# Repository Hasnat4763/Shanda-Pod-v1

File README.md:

# Shanda Pod

It is an MP3 player which can also play audio via bluetooth A2DP source and a PCM5102A module

I made this project because I wanted to experiment with mp3 players and I need an mp3 player with bluetooth outputs

# PCB

This is the Schematic

This is the PCB

PCB 3D View

# CAD

I designed it in Fusion360 which was pretty hard as it crashed idk why
This is all the parts fitted together

This is a cover which will sit on top of the battery

# Schematic

I have some parts outside of my PCB

# BOM

| Name                                                                  | Qty | Final Price - USD(BDT) | Link                                                                                                                |
| --------------------------------------------------------------------- | --- | ----------------------- | ------------------------------------------------------------------------------------------------------------------- |
| ESP-32-WROVER-E                                                       | 1   | US $7.39                | [here](https://www.aliexpress.com/item/1005008347478258.html?spm=a2g0o.cart.0.0.35b638daQUHsS4&mp=1)                                                             |
| NASAYI 10pcs/lot DM3AT-SF-PEJM5                                       | 10  | US $8.63                | [here](https://www.aliexpress.com/item/1005009250329013.html?spm=a2g0o.cart.0.0.35b638daQUHsS4&mp=1&pdp_ext_f=%7B%22cart2PdpParams%22%3A%7B%22pdpBusinessMode%22%3A%22retail%22%7D%7D)                                  |
| CH340C sop-16 Chipset                                                 | 5   | US $1.44                | [here](https://www.aliexpress.com/item/1005004970840775.html?spm=a2g0o.cart.0.0.35b638daQUHsS4&mp=1)                                           |
| 6092 bq25185 USB / DC / Solar Charger with 3.3V Buck Board            | 1   | US $13.66               | [here](https://www.aliexpress.com/item/1005008651296534.html?spm=a2g0o.cart.0.0.35b638daQUHsS4&mp=1)                                                                |
| 100NF 0.1UF 50V C0805 Capacitor                                       | 100 | US $0.73                | [here](https://www.aliexpress.com/item/1115774532.html?spm=a2g0o.cart.0.0.35b638daQUHsS4&mp=1)                                                                                   |
|  SSD1306                                                              | 1   | US $1.42                | [here](https://www.aliexpress.com/item/1005003780343300.html?spm=a2g0o.cart.0.0.35b638daQUHsS4&mp=1)                                                                                   |
| PCM5102A DAC                                                          | 1   | US $4.05                | [here](https://www.aliexpress.com/item/1005006104368969.html?spm=a2g0o.cart.0.0.35b638daQUHsS4&mp=1)                                                                                   |
| Insert M1.6 Brass Heat Threaded Insert Nut and Stainless Steel Screw  |set  | US $15.02               | [here](https://www.aliexpress.com/item/1005004837433548.html?spm=a2g0o.cart.0.0.35b638daQUHsS4&mp=1)                                                                                   |
| MHP30 Mini Hot Plate                                                  | 1   | US $13.52               | [here](https://www.aliexpress.com/item/1005005887052045.html?spm=a2g0o.cart.0.0.72f938daHYVVmK&mp=1)          |
| 18650 Lithium-ion                                                     | 2   | 348 BDT                 | [here](https://www.daraz.com.bd//products/i337388376-s1645620986.html?spm=a2o42.cart.0.0.5b8f282903B5mN&urlFlag=true&tradePath=%2CcartPriceDrop%2Ccart)                                           |
| PCB                                                                   | 5   | US $26.68               | [here](https://hc-cdn.hel1.your-objectstorage.com/s/v3/ba1be02d5d65575ba7409b266db8009ed1d59e8f_image.png)                                          |
| Stencil                                                               | 1   | US $$8.90               | [here](https://hc-cdn.hel1.your-objectstorage.com/s/v3/ba1be02d5d65575ba7409b266db8009ed1d59e8f_image.png)                                         |                                                                                 |
| Soldering Paste                                                       | 1   | US $3.81                | [here](https://www.aliexpress.com/item/1005009298760047.html?spm=a2g0o.productlist.main.11.11a96444UURzz6&algo_pvid=175fc725-feab-48a3-bc75-27a2c631128b&pdp_ext_f=%7B%22order%22%3A%22880%22%2C%22eval%22%3A%221%22%7D&utparam-url=scene%3Asearch%7Cquery_from%3A)                                         |        
| Top Case                                                              | 1   | Printing Legion         | 
| Bottom Case                                                           | 1   | Printing Legion         |
| Battery Cover                                                         | 1   | Printing Legion         |

# Total Cost: ~ 115$ USD

# Why is this too exbensive?

Check this out

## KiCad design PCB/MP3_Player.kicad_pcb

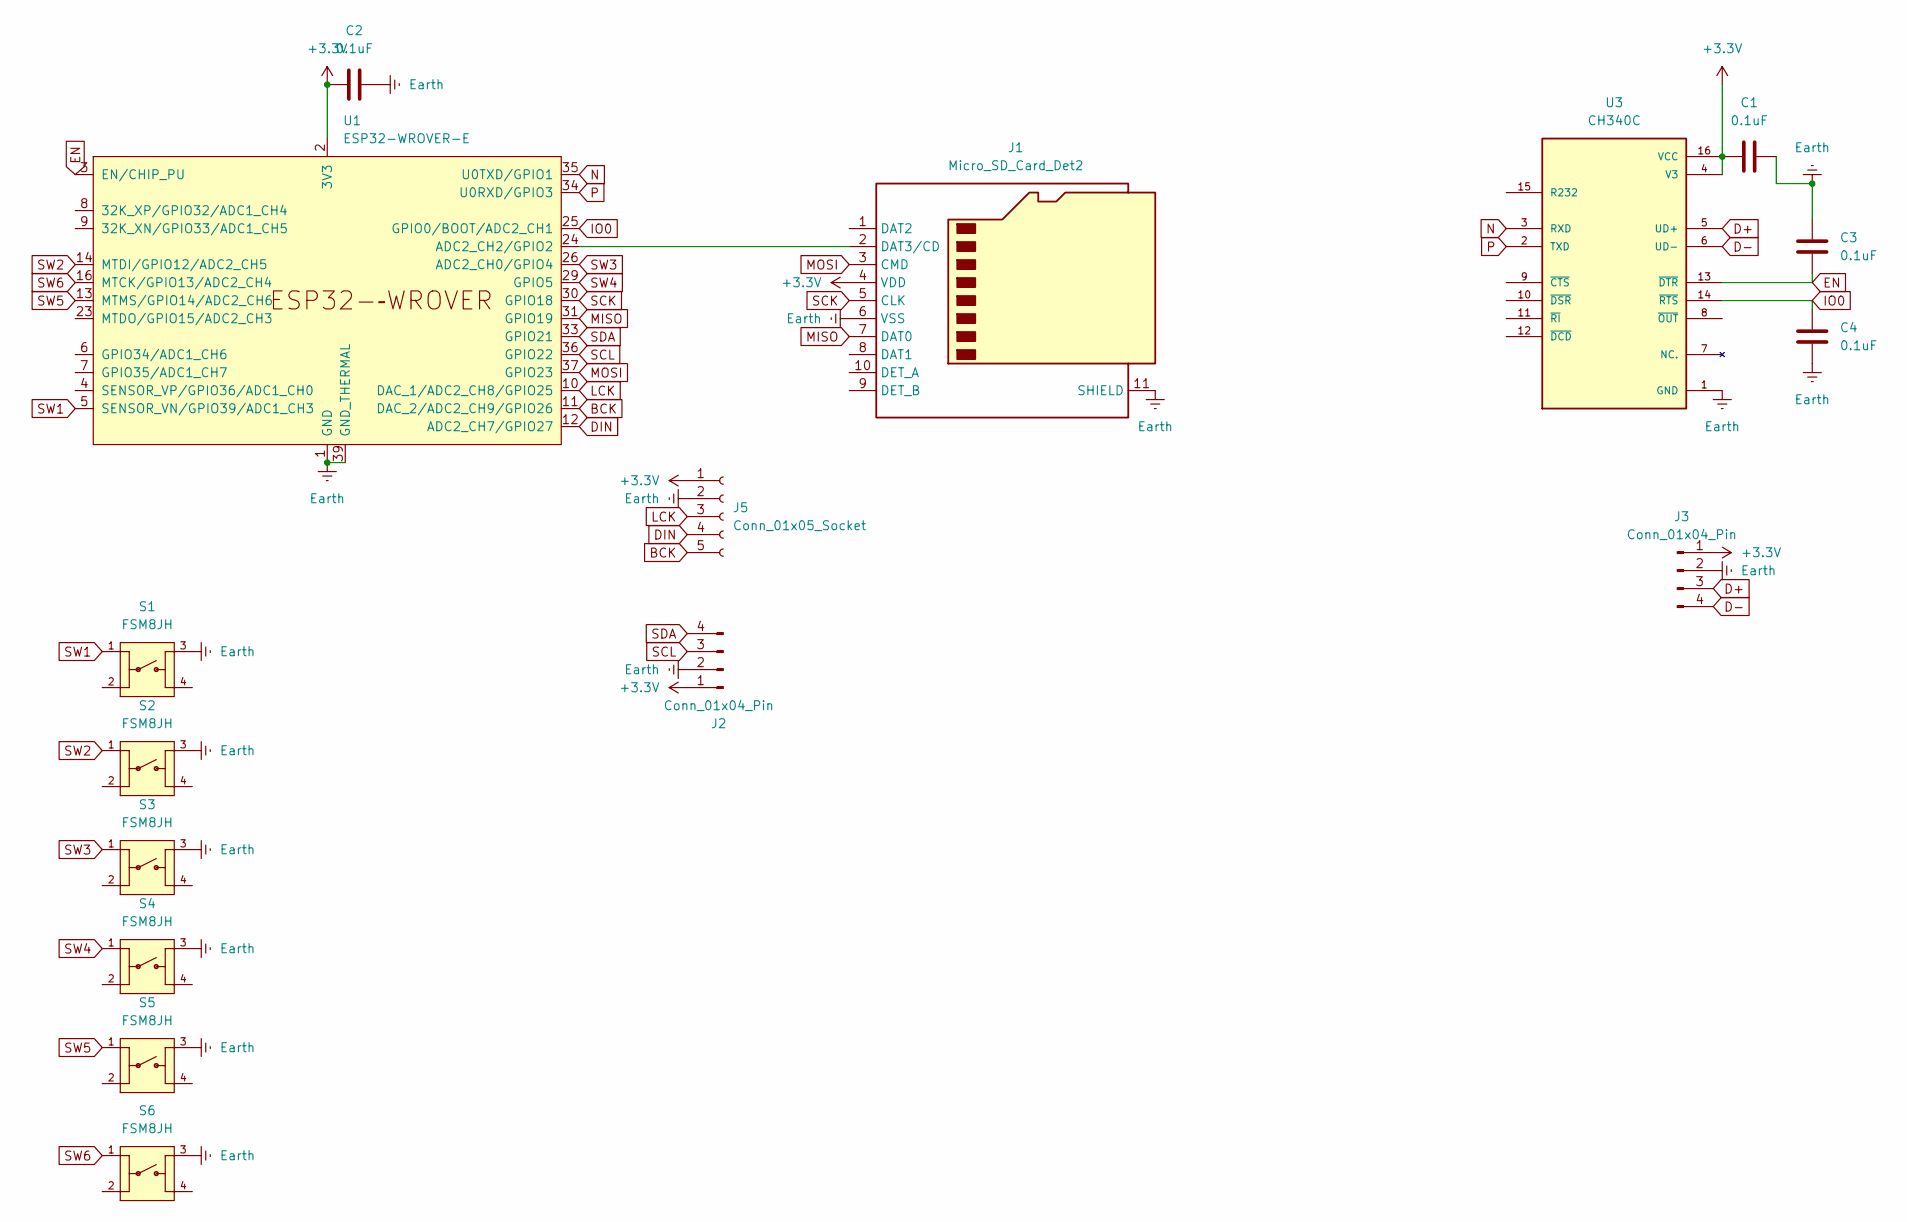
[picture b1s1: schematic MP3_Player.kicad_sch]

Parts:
C1, C2, C3, C4: 0.1uF; C_0805_2012Metric
J1: Micro_SD_Card_Det2; microSD_HC_Hirose_DM3AT-SF-PEJM5
J2: Conn_01x04_Pin; MODULE_DM-OLED096-636
J3: Conn_01x04_Pin; PinHeader_1x04_P1.27mm_Vertical
J5: Conn_01x05_Socket; PinHeader_1x05_P1.00mm_Horizontal
S1, S2, S3, S4, S5, S6: FSM8JH; SW_FSM8JH; PARTREV C10
U1: ESP32-WROVER-E
U3: CH340C; SOIC127P600X180-16N; PARTREV 2G

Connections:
+3.3V: C1.1, C2.1, J1.4 (VDD), J2.1, J3.1, J5.1, U1.2 (3V3), U3.4 (V3), U3.16 (VCC)
BCK: J5.5, U1.11 (DAC_2/ADC2_CH9/GPIO26)
D+: J3.3, U3.5 (UD+)
D-: J3.4, U3.6 (UD-)
DIN: J5.4, U1.12 (ADC2_CH7/GPIO27)
EN: C3.1, U1.3 (EN/CHIP_PU), U3.13 (~DTR)
Earth: C1.2, C2.2, C3.2, C4.1, J1.6 (VSS), J1.11 (SHIELD), J2.2, J3.2, J5.2, S1.3, S2.3, S3.3, S4.3, S5.3, S6.3, U1.1 (GND), U1.15 (GND), U1.38 (GND), U1.39 (GND_THERMAL), U3.1 (GND)
IO0: C4.2, U1.25 (GPIO0/BOOT/ADC2_CH1), U3.14 (~RTS)
LCK: J5.3, U1.10 (DAC_1/ADC2_CH8/GPIO25)
MISO: J1.7 (DAT0), U1.31 (GPIO19)
MOSI: J1.3 (CMD), U1.37 (GPIO23)
N: U1.35 (U0TXD/GPIO1), U3.3 (RXD)
unnamed: J1.2 (DAT3/CD), U1.24 (ADC2_CH2/GPIO2)
P: U1.34 (U0RXD/GPIO3), U3.2 (TXD)
SCK: J1.5 (CLK), U1.30 (GPIO18)
SCL: J2.3, U1.36 (GPIO22)
SDA: J2.4, U1.33 (GPIO21)
SW1: S1.1, U1.5 (SENSOR_VN/GPIO39/ADC1_CH3)
SW2: S2.1, U1.14 (MTDI/GPIO12/ADC2_CH5)
SW3: S3.1, U1.26 (ADC2_CH0/GPIO4)
SW4: S4.1, U1.29 (GPIO5)
SW5: S5.1, U1.13 (MTMS/GPIO14/ADC2_CH6)
SW6: S6.1, U1.16 (MTCK/GPIO13/ADC2_CH4)

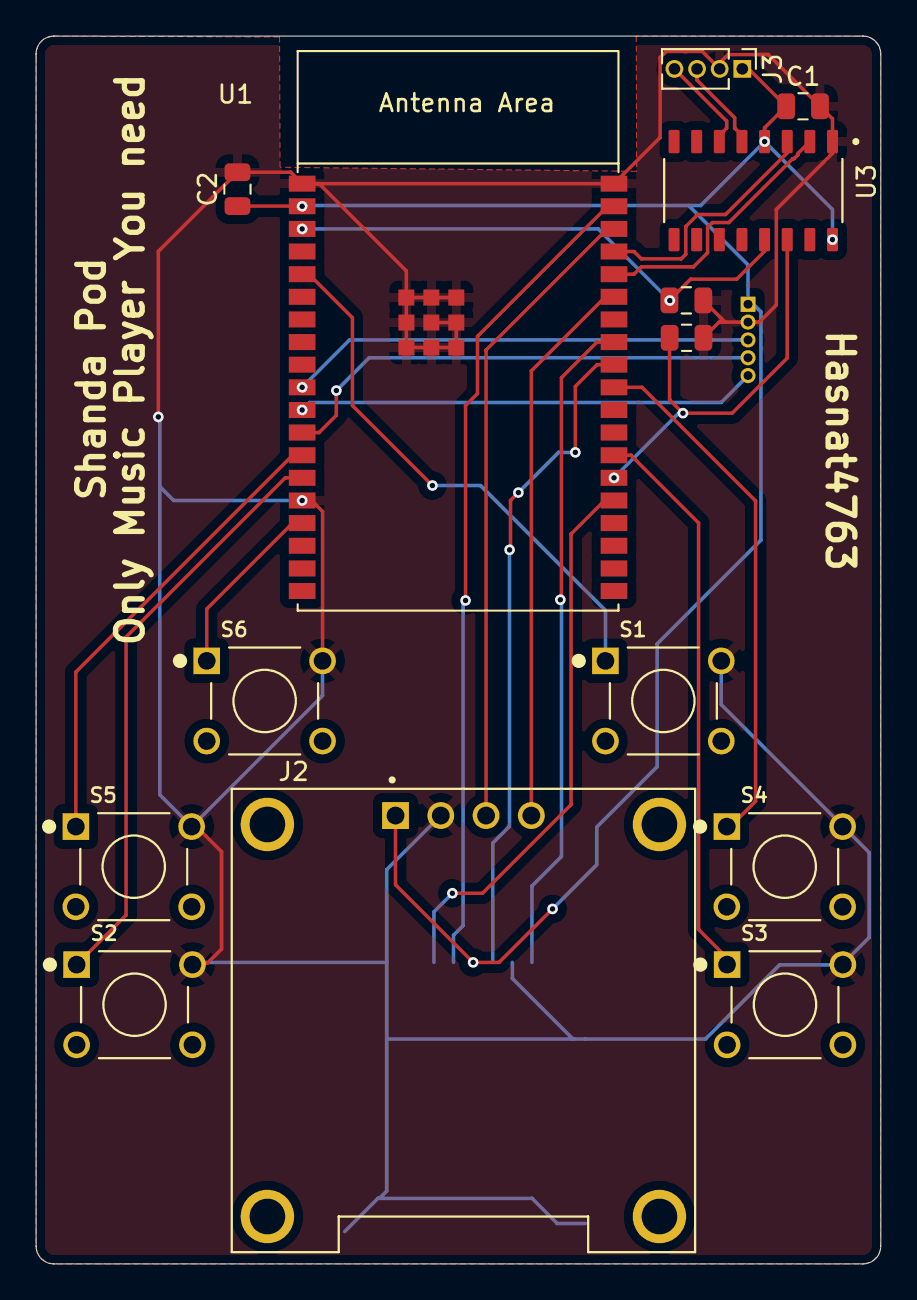
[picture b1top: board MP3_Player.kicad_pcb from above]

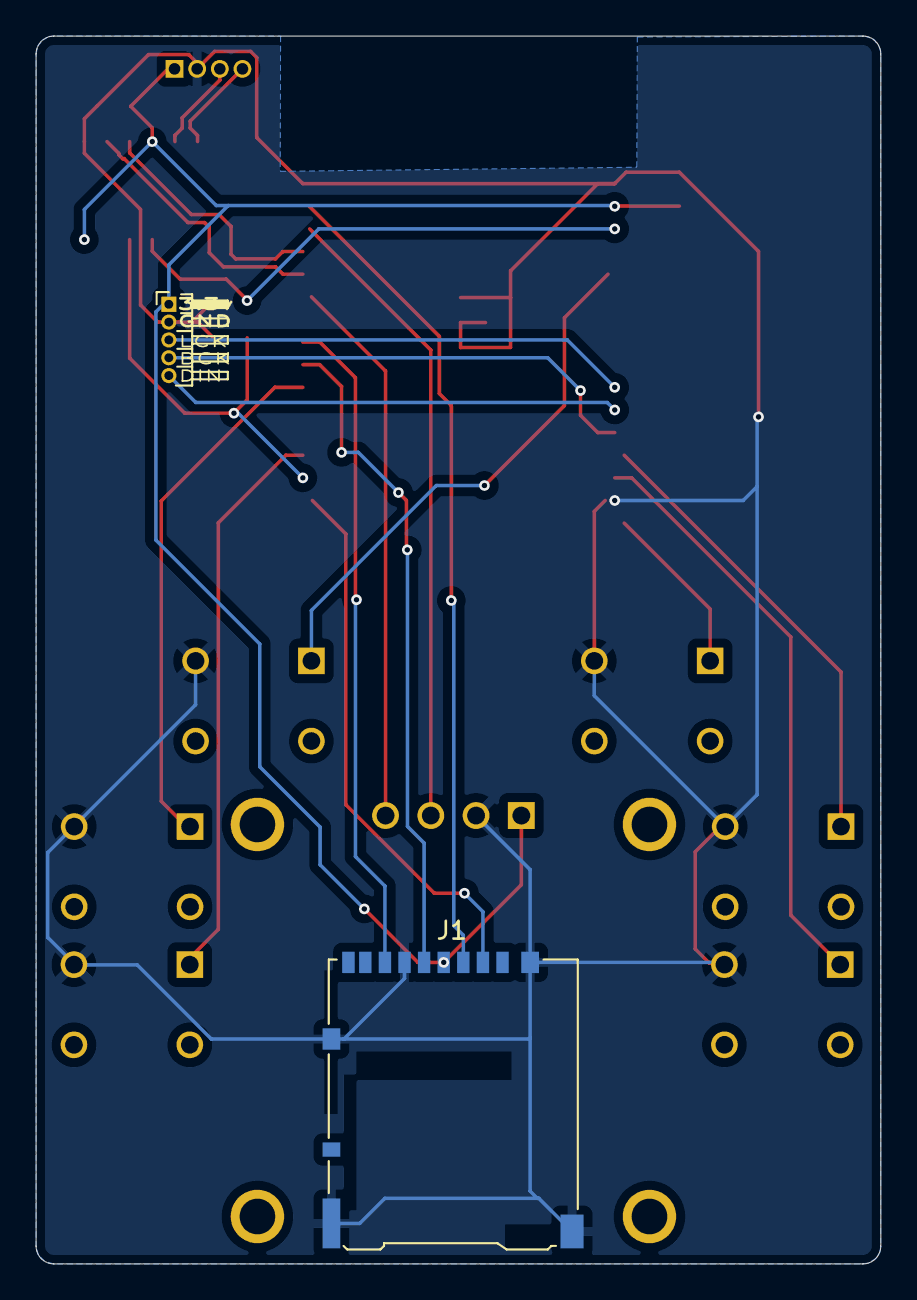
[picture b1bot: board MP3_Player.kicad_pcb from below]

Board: 2 copper layers, 47.4 x 68.9 mm, 16 parts (2 on the bottom side), 23 nets.

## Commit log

2025-07-05 Adding files
2025-07-12 Updating
2025-07-12 Change
